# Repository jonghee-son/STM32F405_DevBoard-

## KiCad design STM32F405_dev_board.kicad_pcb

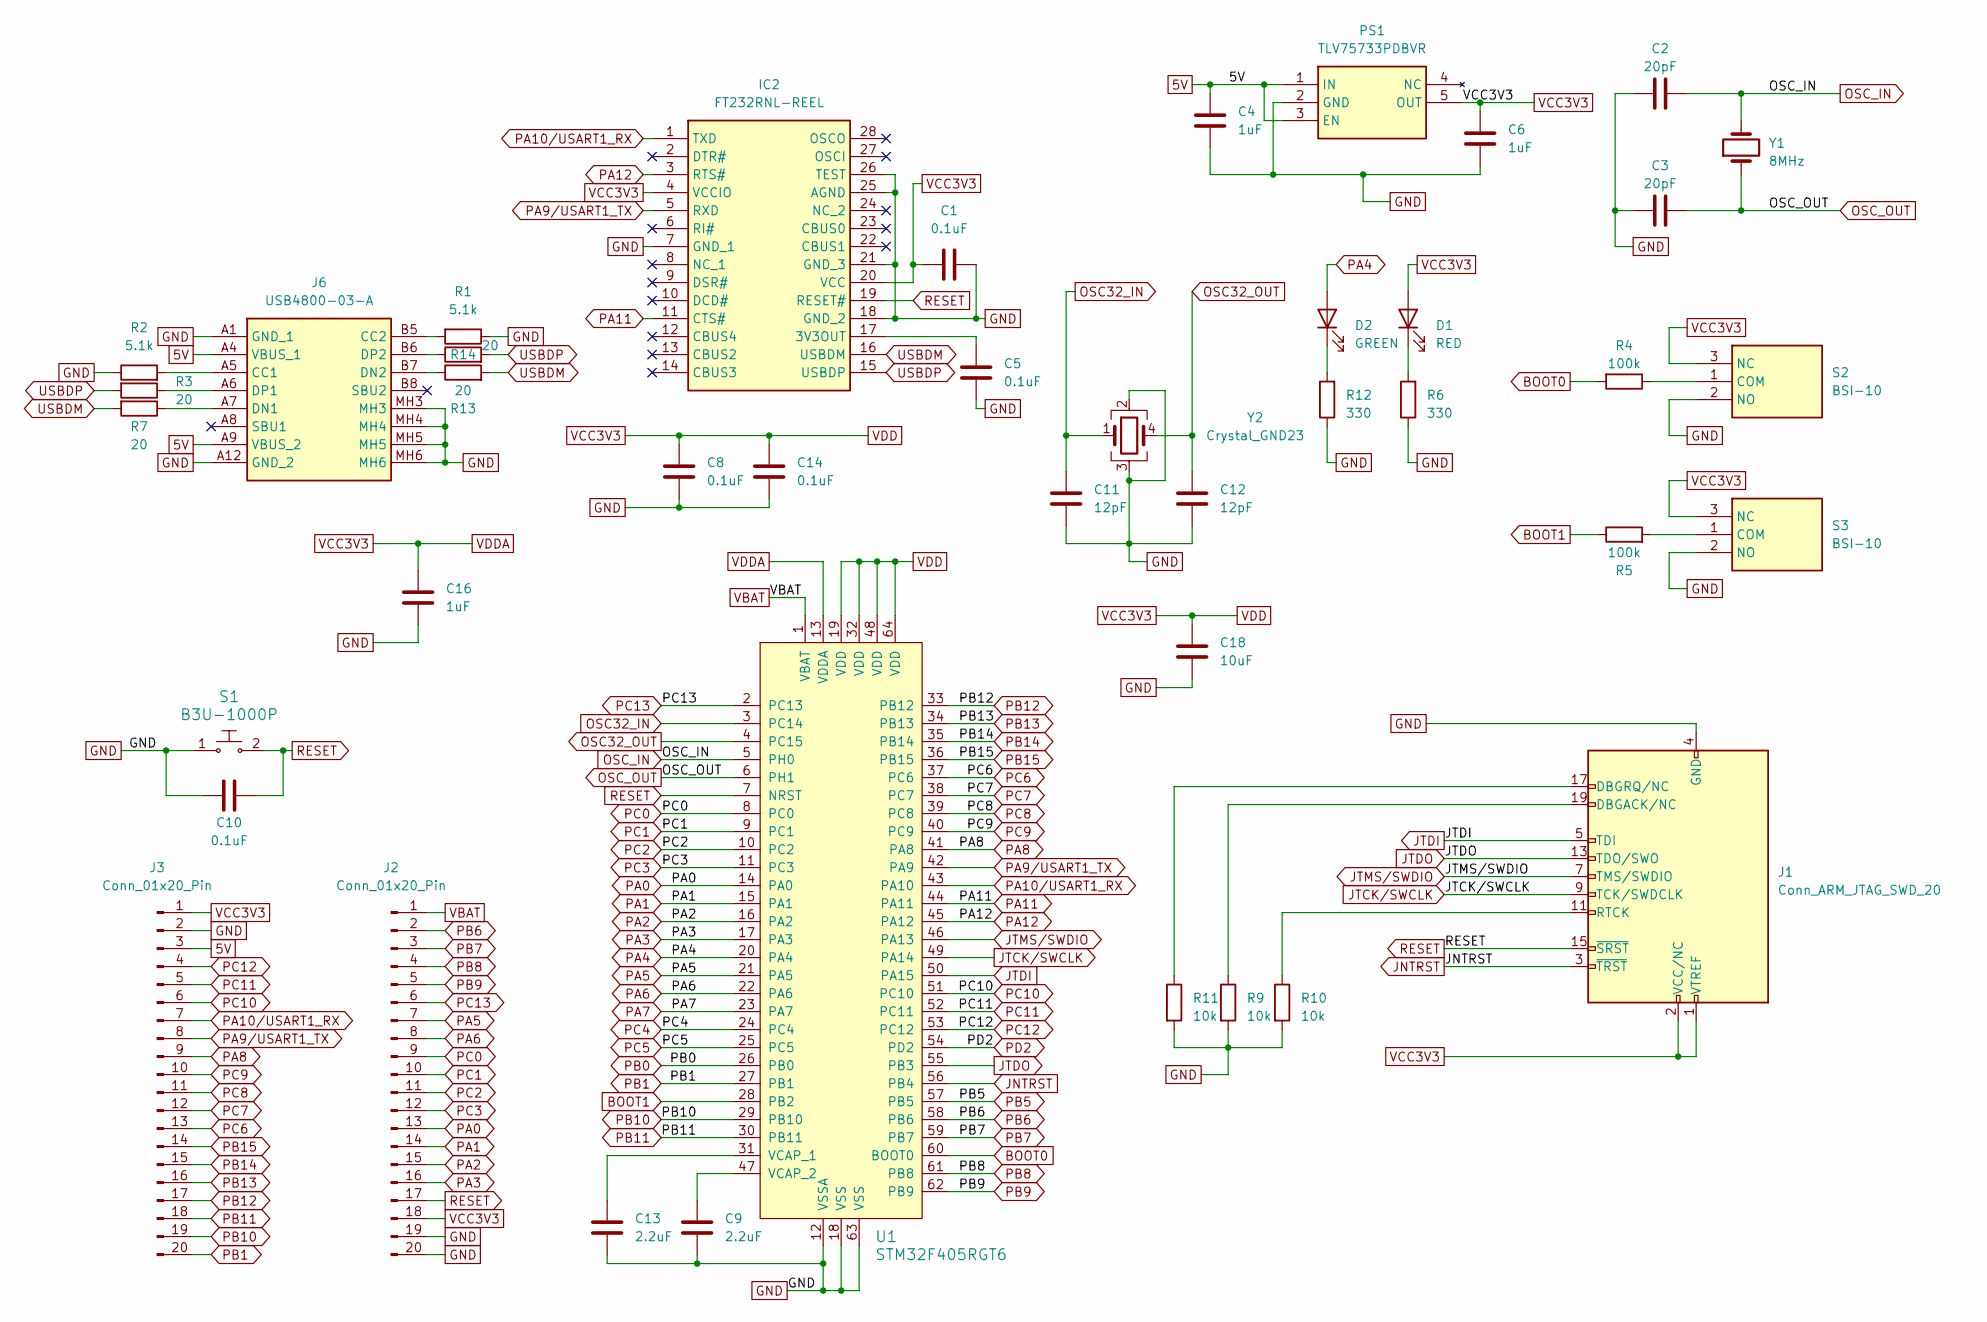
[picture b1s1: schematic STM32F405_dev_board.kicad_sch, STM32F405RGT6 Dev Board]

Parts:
C1, C5, C8, C10, C14: 0.1uF; C_0603_1608Metric_Pad1.08x0.95mm_HandSolder
C2, C3: 20pF; C_0603_1608Metric_Pad1.08x0.95mm_HandSolder
C4, C6, C16: 1uF; C_0603_1608Metric_Pad1.08x0.95mm_HandSolder
C9, C13: 2.2uF; C_0603_1608Metric_Pad1.08x0.95mm_HandSolder
C11, C12: 12pF; C_0603_1608Metric_Pad1.08x0.95mm_HandSolder
C18: 10uF; C_0603_1608Metric_Pad1.08x0.95mm_HandSolder
D1: RED; LED_0603_1608Metric_Pad1.05x0.95mm_HandSolder
D2: GREEN; LED_0603_1608Metric_Pad1.05x0.95mm_HandSolder
IC2: FT232RNL-REEL; SOP65P780X200-28N; Mouser Part Number 895-FT232RNL-REEL
J1: Conn_ARM_JTAG_SWD_20; IDC-Header_2x10_P2.54mm_Vertical
J2, J3: Conn_01x20_Pin; PinHeader_1x20_P2.54mm_Vertical
J6: USB4800-03-A; USB480003A; Mouser Part Number 640-USB4800-03-A
PS1: TLV75733PDBVR; SOT95P280X145-5N; Manufacturer_Part_Number TLV75733PDBVR; Mouser Part Number 595-TLV75733PDBVR
R1, R2: 5.1k; R_0603_1608Metric_Pad0.98x0.95mm_HandSolder
R3, R7, R13, R14: 20; R_0603_1608Metric_Pad0.98x0.95mm_HandSolder
R4, R5: 100k; R_0603_1608Metric_Pad0.98x0.95mm_HandSolder
R6, R12: 330; R_0603_1608Metric_Pad0.98x0.95mm_HandSolder
R9, R10, R11: 10k; R_0603_1608Metric_Pad0.98x0.95mm_HandSolder
S1: B3U-1000P; Switch_Tactile_SMD_B3U-1000P; MPN B3U-1000P; Digi-Key_PN SW1020CT-ND
S2, S3: BSI-10; BSI10; Manufacturer_Part_Number BSI-10
U1: STM32F405RGT6; LQFP-64_10x10mm; MPN STM32F405RGT6; Digi-Key_PN 497-11767-ND
Y1: 8MHz; Crystal_SMD_HC49-SD_HandSoldering
Y2: Crystal_GND23; Crystal_SMD_SeikoEpson_MC306-4Pin_8.0x3.2mm_HandSoldering

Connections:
5V: C4.2, J3.3, J6.A4 (VBUS_1), J6.A9 (VBUS_2), PS1.1 (IN), PS1.3 (EN)
BOOT0: R4.2, U1.60 (BOOT0)
BOOT1: R5.1, U1.28 (PB2)
GND: C1.1, C2.1, C3.1, C4.1, C5.1, C6.1, C8.1, C9.1, C10.2, C11.1, C12.1, C13.1, C14.1, C16.1, C18.1, IC2.7 (GND_1), IC2.18 (GND_2), IC2.21 (GND_3), IC2.25 (AGND), IC2.26 (TEST), J1.4 (GND), J1.6 (GND), J1.8 (GND), J1.10 (GND), J1.12 (GND), J1.14 (GND), J1.16 (GND), J1.18 (GND), J1.20 (GND), J2.19, J2.20, J3.2, J6.A1 (GND_1), J6.A12 (GND_2), J6.MH3, J6.MH4, J6.MH5, J6.MH6, PS1.2 (GND), R1.1, R2.1, R6.1, R9.2, R10.2, R11.2, R12.1, S1.1, S2.2 (NO), S3.2 (NO), U1.12 (VSSA), U1.18 (VSS), U1.63 (VSS), Y2.2, Y2.3
JNTRST: J1.3 (~TRST), U1.56 (PB4)
JTCK/SWCLK: J1.9 (TCK/SWDCLK), U1.49 (PA14)
JTDI: J1.5 (TDI), U1.50 (PA15)
JTDO: J1.13 (TDO/SWO), U1.55 (PB3)
JTMS/SWDIO: J1.7 (TMS/SWDIO), U1.46 (PA13)
unnamed: D1.1 (K), R6.2
unnamed: D2.1 (K), R12.2
unnamed: C5.2, IC2.17 (3V3OUT)
unnamed: J1.19 (DBGACK/NC), R9.1
unnamed: J1.17 (DBGRQ/NC), R11.1
unnamed: J1.11 (RTCK), R10.1
unnamed: J6.A5 (CC1), R2.2
unnamed: J6.B5 (CC2), R1.2
unnamed: J6.A7 (DN1), R7.1
unnamed: J6.B7 (DN2), R13.1
unnamed: J6.A6 (DP1), R3.1
unnamed: J6.B6 (DP2), R14.1
unnamed: R4.1, S2.1 (COM)
unnamed: R5.2, S3.1 (COM)
unnamed: C13.2, U1.31 (VCAP_1)
unnamed: C9.2, U1.47 (VCAP_2)
OSC32_IN: C11.2, U1.3 (PC14), Y2.1
OSC32_OUT: C12.2, U1.4 (PC15), Y2.4
OSC_IN: C2.2, U1.5 (PH0), Y1.2
OSC_OUT: C3.2, U1.6 (PH1), Y1.1
PA0: J2.13, U1.14 (PA0)
PA1: J2.14, U1.15 (PA1)
PA2: J2.15, U1.16 (PA2)
PA3: J2.16, U1.17 (PA3)
PA4: D2.2 (A), U1.20 (PA4)
PA5: J2.7, U1.21 (PA5)
PA6: J2.8, U1.22 (PA6)
PA7: U1.23 (PA7)
PA8: J3.9, U1.41 (PA8)
PA9/USART1_TX: IC2.5 (RXD), J3.8, U1.42 (PA9)
PA10/USART1_RX: IC2.1 (TXD), J3.7, U1.43 (PA10)
PA11: IC2.11 (CTS#), U1.44 (PA11)
PA12: IC2.3 (RTS#), U1.45 (PA12)
PB0: U1.26 (PB0)
PB1: J3.20, U1.27 (PB1)
PB5: U1.57 (PB5)
PB6: J2.2, U1.58 (PB6)
PB7: J2.3, U1.59 (PB7)
PB8: J2.4, U1.61 (PB8)
PB9: J2.5, U1.62 (PB9)
PB10: J3.19, U1.29 (PB10)
PB11: J3.18, U1.30 (PB11)
PB12: J3.17, U1.33 (PB12)
PB13: J3.16, U1.34 (PB13)
PB14: J3.15, U1.35 (PB14)
PB15: J3.14, U1.36 (PB15)
PC0: J2.9, U1.8 (PC0)
PC1: J2.10, U1.9 (PC1)
PC2: J2.11, U1.10 (PC2)
PC3: J2.12, U1.11 (PC3)
PC4: U1.24 (PC4)
PC5: U1.25 (PC5)
PC6: J3.13, U1.37 (PC6)
PC7: J3.12, U1.38 (PC7)
PC8: J3.11, U1.39 (PC8)
PC9: J3.10, U1.40 (PC9)
PC10: J3.6, U1.51 (PC10)
PC11: J3.5, U1.52 (PC11)
PC12: J3.4, U1.53 (PC12)
PC13: J2.6, U1.2 (PC13)
PD2: U1.54 (PD2)
RESET: C10.1, IC2.19 (RESET#), J1.15 (~SRST), J2.17, S1.2, U1.7 (NRST)
USBDM: IC2.16 (USBDM), R7.2, R13.2
USBDP: IC2.15 (USBDP), R3.2, R14.2
VBAT: J2.1, U1.1 (VBAT)
VCC3V3: C1.2, C6.2, C8.2, C14.2, C16.2, C18.2, D1.2 (A), IC2.4 (VCCIO), IC2.20 (VCC), J1.1 (VTREF), J1.2 (VCC/NC), J2.18, J3.1, PS1.5 (OUT), S2.3 (NC), S3.3 (NC), U1.13 (VDDA), U1.19 (VDD), U1.32 (VDD), U1.48 (VDD), U1.64 (VDD)

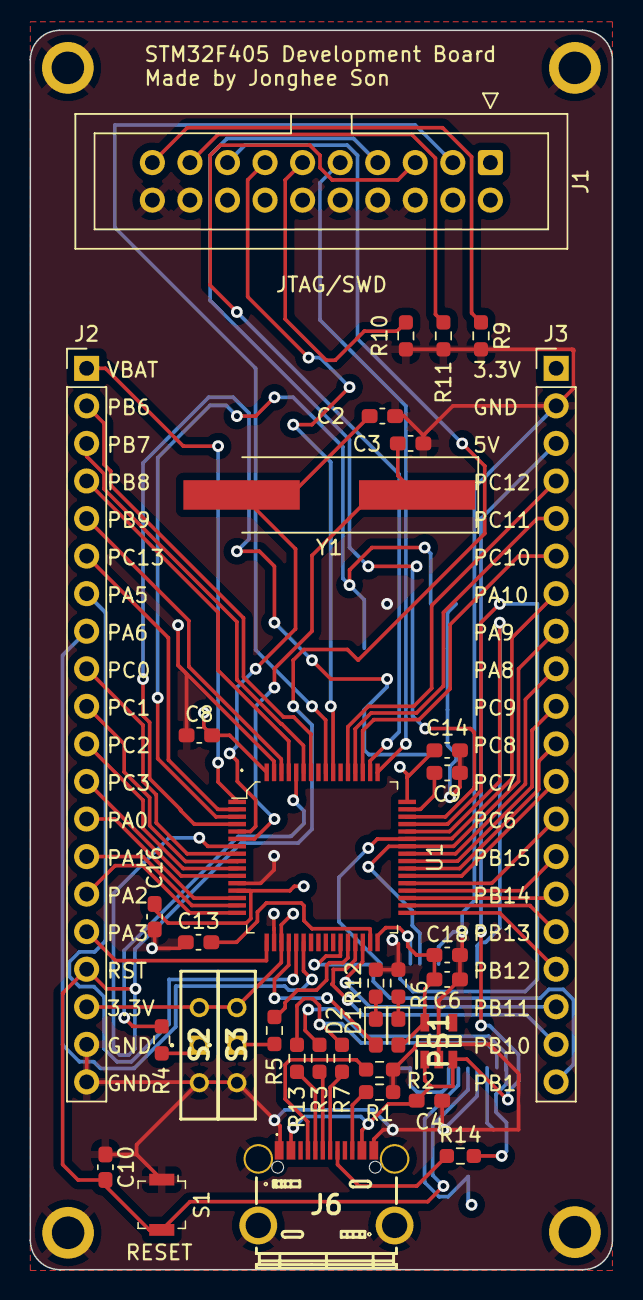
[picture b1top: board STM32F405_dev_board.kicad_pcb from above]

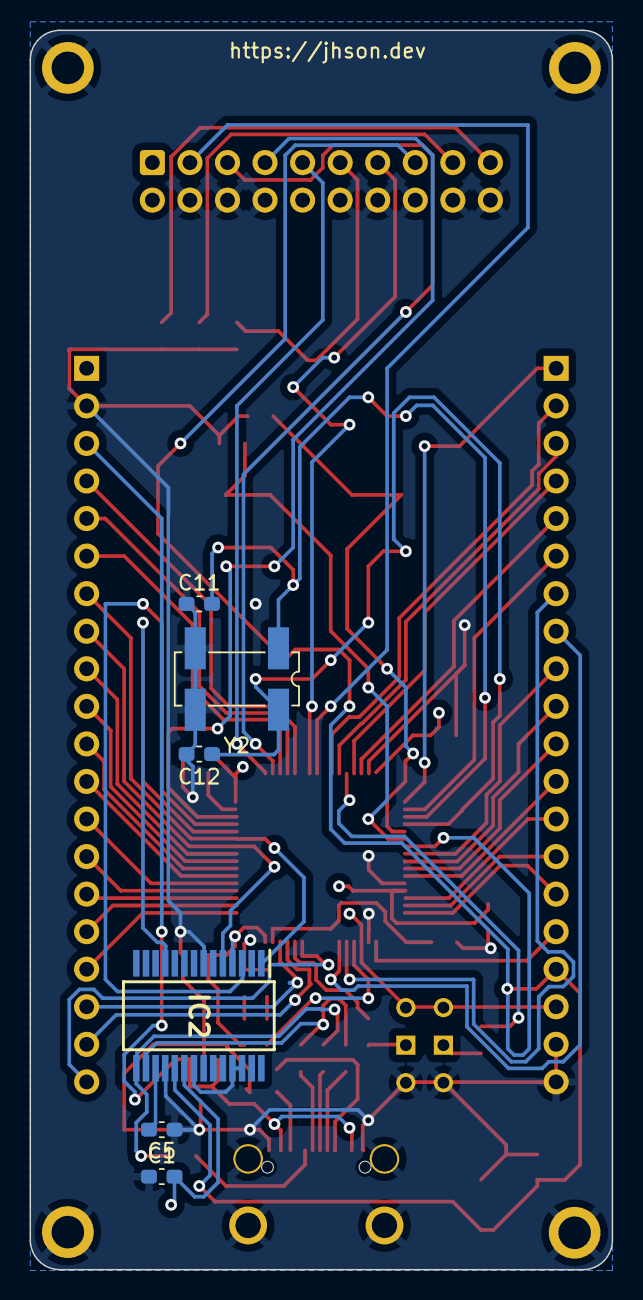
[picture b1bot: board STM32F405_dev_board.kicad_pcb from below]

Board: 4 copper layers, 39.4 x 83.8 mm, 42 parts (6 on the bottom side), 69 nets.

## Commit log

2023-12-15 Changed board marking
2023-12-16 Changed silkscreen overwraps
2023-12-21 Changed 8MHz oscillator to SMD one
2023-12-21 Fixed BOM
2024-03-15 Fixed FT232RL connection
